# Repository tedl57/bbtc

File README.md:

# bbtc
Battery Box Temperature Controller

The BBTC is an Arduino-based circuit that independently measures and controls the temperatures of up to 4 battery boxes.

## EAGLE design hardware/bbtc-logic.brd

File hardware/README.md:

# bbtc-hardware
Battery Box Temperature Controller Hardware

These are the Eagle (cadsoft) schematics and board layouts for the logic and relay boards.

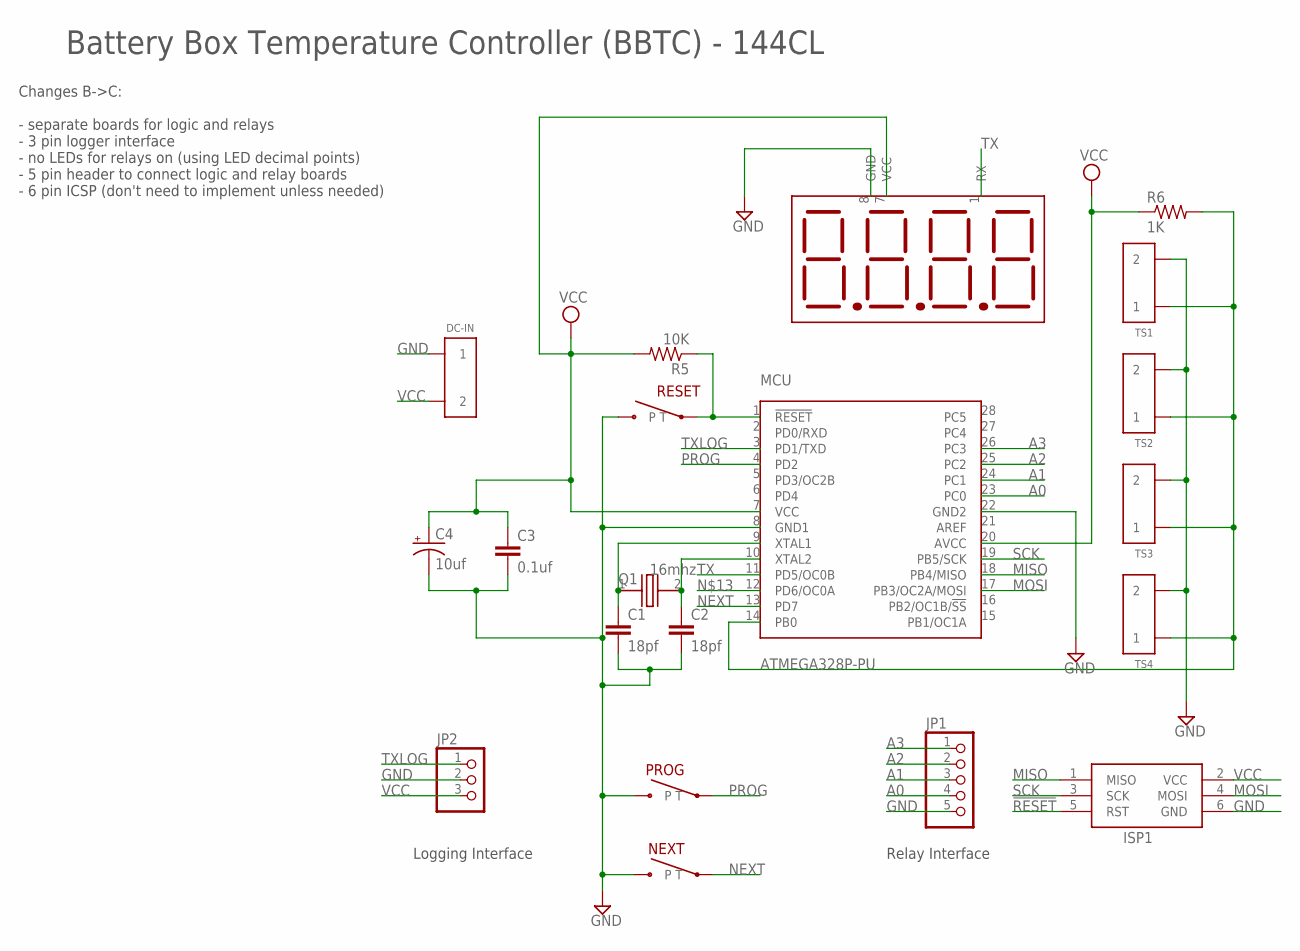
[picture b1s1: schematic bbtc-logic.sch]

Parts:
4-DIG-DISPLAY: 4-DIGIT-DISPLAY; 3SIL-OF-8
C1, C2: 18pf; C0805
C3: 0.1uf; C0805
C4: 10uf; E2-4
DC-IN: SCREW-CLAMP-1255; SCREW-CLAMP-ADAFRUIT-2X3.5MM
ISP1: AVRISP-6; AVRISP
JP1: PINHD-1X5; 1X05
JP2: PINHD-1X3; 1X03
MCU: ATMEGA328P-PU; DIL28-3
NEXT: SWITCH-SPST-NEW; SWITCH-ADAFRUIT-6MM-SLIM
PROG: SWITCH-SPST-NEW; SWITCH-ADAFRUIT-6MM-SLIM
Q1: 16mhz; CRYSTAL-5X3.2MM-1024
R5: 10K; R0805
R6: 1K; M0805
RESET: SWITCH-SPST-NEW; SWITCH-ADAFRUIT-6MM-SLIM
TS1, TS2, TS3, TS4: SCREW-CLAMP-1255; SCREW-CLAMP-ADAFRUIT-2X3.5MM

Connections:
1W: MCU.14 (PB0), R6.2, TS1.1, TS2.1, TS3.1, TS4.1
!RESET: ISP1.5 (RST), MCU.1 (!RESET), R5.1, RESET.T
A0: JP1.4, MCU.23 (PC0)
A1: JP1.3, MCU.24 (PC1)
A2: JP1.2, MCU.25 (PC2)
A3: JP1.1, MCU.26 (PC3)
GND: 4-DIG-DISPLAY.8 (GND), C1.2, C2.2, C3.2, C4.-, DC-IN.1, ISP1.6 (GND), JP1.5, JP2.2, MCU.8 (GND1), MCU.22 (GND2), NEXT.P, PROG.P, RESET.P, TS1.2, TS2.2, TS3.2, TS4.2
MISO: ISP1.1 (MISO), MCU.18 (PB4/MISO)
MOSI: ISP1.4 (MOSI), MCU.17 (PB3/OC2A/MOSI)
unnamed: C1.1, MCU.9 (XTAL1), Q1.1
unnamed: C2.1, MCU.10 (XTAL2), Q1.2
NEXT: MCU.13 (PD7), NEXT.T
PROG: MCU.4 (PD2), PROG.T
SCK: ISP1.3 (SCK), MCU.19 (PB5/SCK)
TX: 4-DIG-DISPLAY.1 (RX), MCU.11 (PD5/OC0B)
TXLOG: JP2.1, MCU.3 (PD1/TXD)
VCC: 4-DIG-DISPLAY.7 (VCC), C3.1, C4.+, DC-IN.2, ISP1.2 (VCC), JP2.3, MCU.7 (VCC), MCU.20 (AVCC), R5.2, R6.1

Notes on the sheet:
Battery Box Temperature Controller (BBTC) - 144CL
Changes B->C: - separate boards for logic and relays - 3 pin logger interface - no LEDs for relays on (using LED decimal points) - 5 pin header to connect logic and relay boards - 6 pin ICSP (don't need to implement unless needed)
Relay Interface
Logging Interface

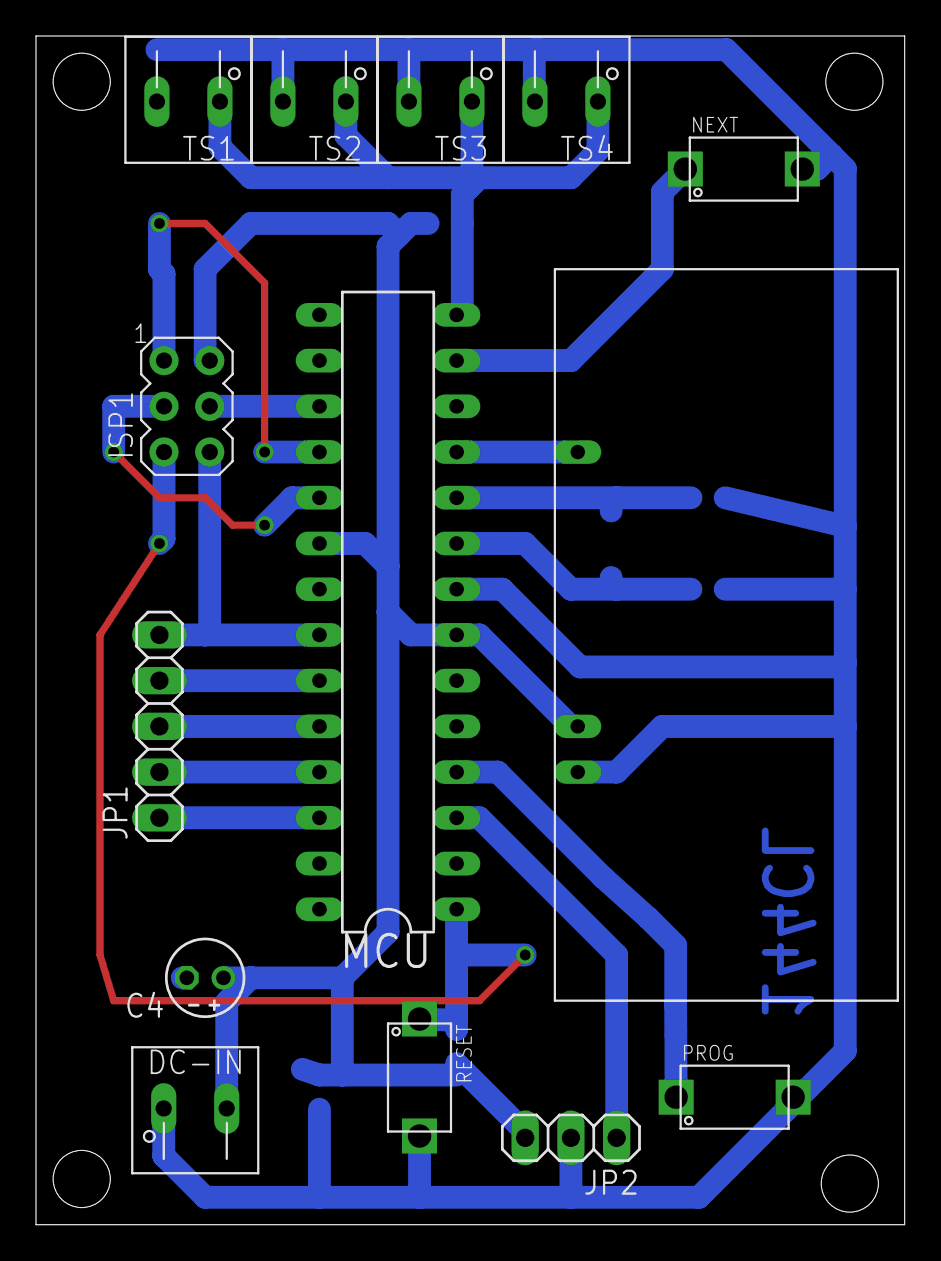
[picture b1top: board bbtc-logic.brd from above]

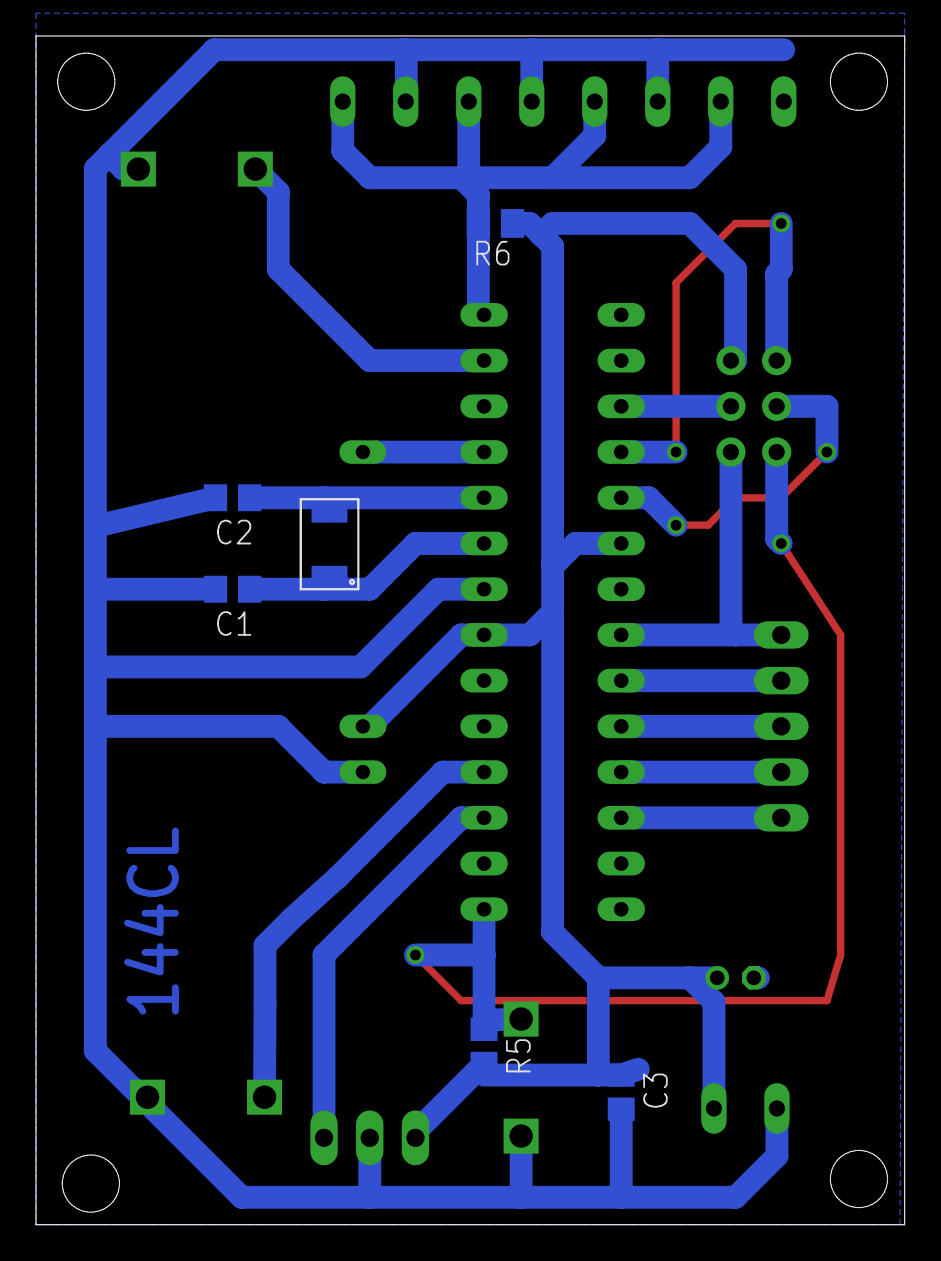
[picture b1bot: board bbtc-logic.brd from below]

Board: 2 copper layers, 48.3 x 66.0 mm, 20 parts (6 on the bottom side), 17 nets.

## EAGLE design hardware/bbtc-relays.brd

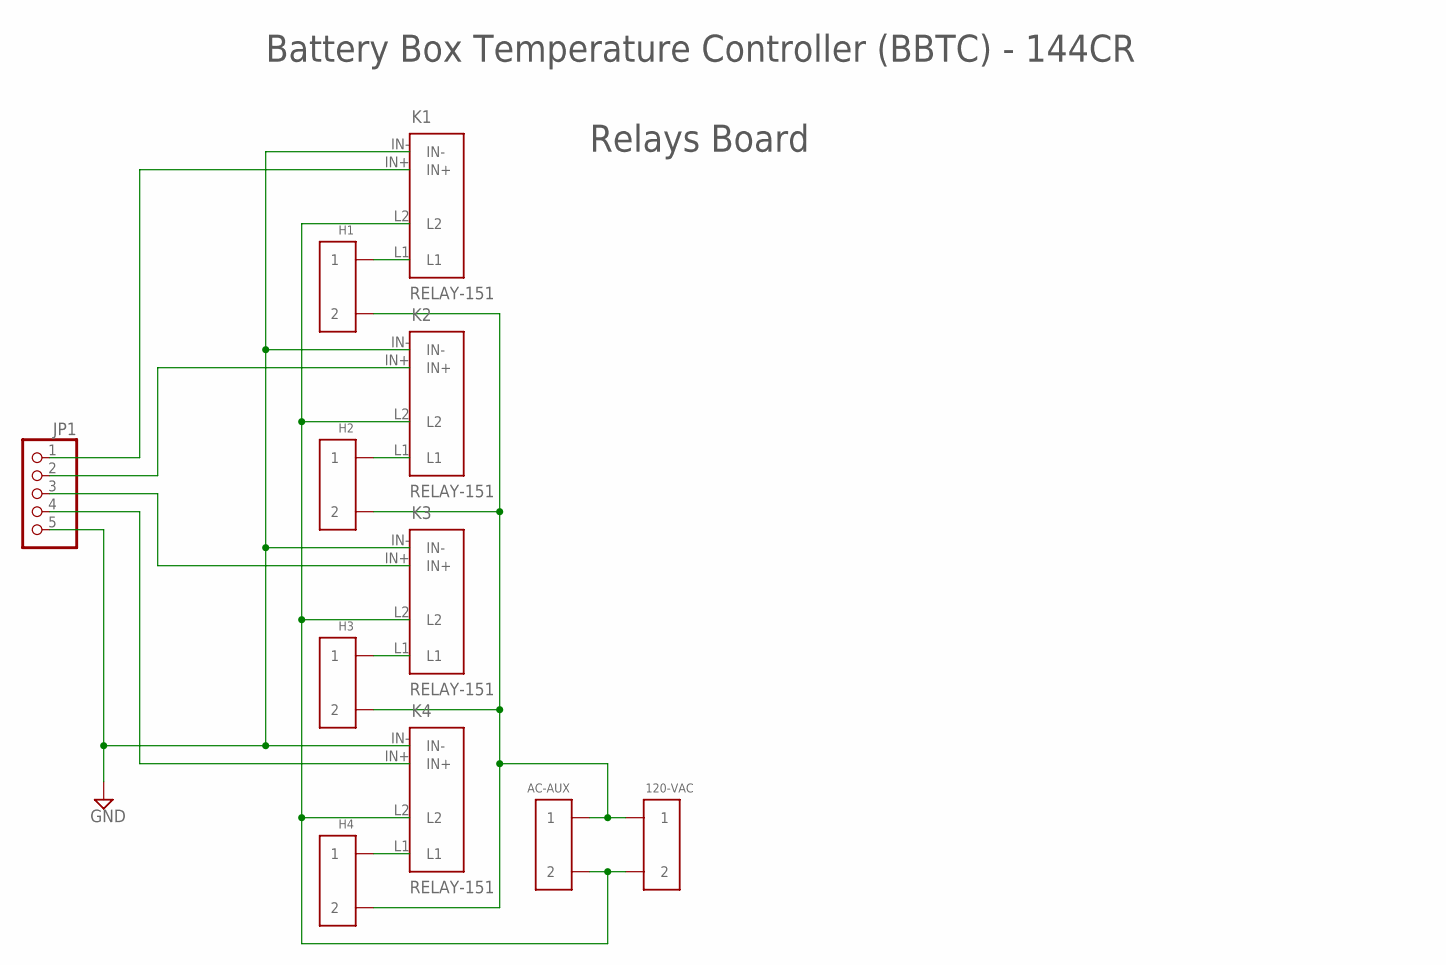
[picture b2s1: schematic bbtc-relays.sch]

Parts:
120-VAC: SCREW-CLAMP-906
AC-AUX: SCREW-CLAMP-909
H1, H2, H3, H4: SCREW-CLAMP-906
JP1: PINHD-1X5; 1X05
K1, K2, K3, K4: RELAY-151

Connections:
GND: JP1.5, K1.IN-, K2.IN-, K3.IN-, K4.IN-
L1: 120-VAC.1, AC-AUX.1, H1.2, H2.2, H3.2, H4.2
L2: 120-VAC.2, AC-AUX.2, K1.L2, K2.L2, K3.L2, K4.L2
unnamed: H4.1, K4.L1
unnamed: H3.1, K3.L1
unnamed: JP1.1, K1.IN+
unnamed: H2.1, K2.L1
unnamed: H1.1, K1.L1
unnamed: JP1.2, K2.IN+
unnamed: JP1.3, K3.IN+
unnamed: JP1.4, K4.IN+

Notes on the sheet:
Battery Box Temperature Controller (BBTC) - 144CR
Relays Board

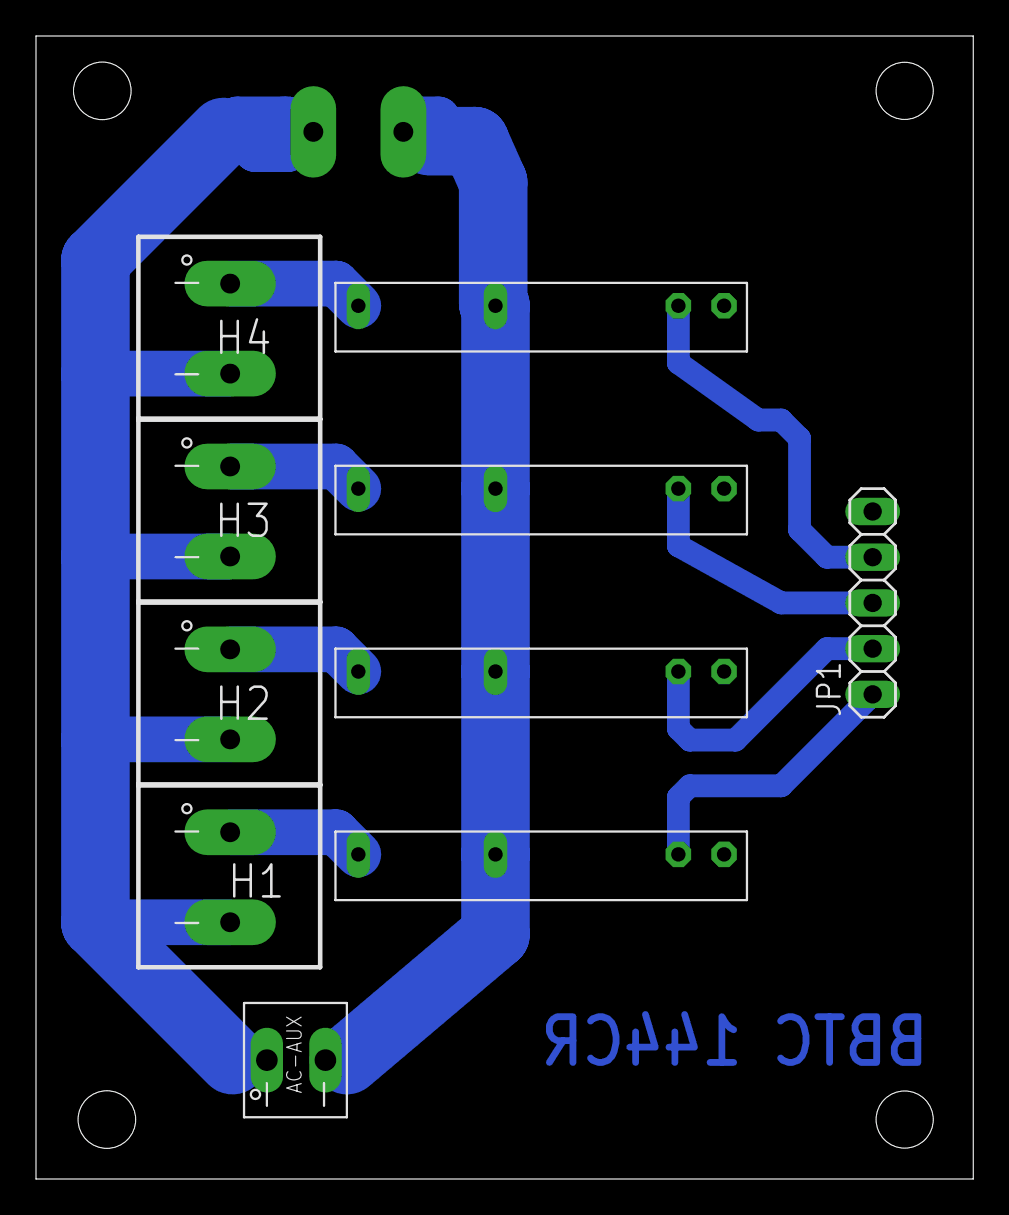
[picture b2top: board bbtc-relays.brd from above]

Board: 2 copper layers, 52.1 x 63.5 mm, 11 parts (1 on the bottom side), 11 nets.

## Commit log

2015-06-03 Post snapshot for Luke
